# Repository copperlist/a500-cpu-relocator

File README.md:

# CopperList CPU-01: Amiga 500 68000 CPU relocator

CPU-01 is CopperList's build of [LinuxJedi's Open68000Relocator](https://github.com/LinuxJedi/Open68000Relocator)
(v2c), which is itself based on [SukkoPera's Open68000Relocator](https://github.com/SukkoPera/Open68000Relocator).
It plugs into the Amiga 500's 68000 socket and turns the CPU 90 degrees, so accelerators such as the TF534 and
TF536 fit. The circuit, the 4-layer routing and LinuxJedi's markings are unchanged; the changes are listed below.

Like the original, CPU-01 is open hardware under the GNU GPL v3 (see [LICENSE](LICENSE)).

## Changes from LinuxJedi's v2c

1. **0805 capacitors.** C1 and C2 (100 nF decoupling, on the underside) use KiCad's 0805 hand-solder footprint
   instead of 0603, in the same places and on the same nets.
2. **Clear CPU outlines and pin-1 notches.**
   - Original CPU position (the pins that go into the motherboard socket): a full outline with a large filled
     pin-1 notch, on the underside (what you see when lining the board up with the socket) and on the top. On
     the top it stops where the relocated socket's outline starts.
   - Relocated socket (where the CPU goes): the outline is redrawn with a large filled notch, kept clear of the
     board edge so it is not trimmed. Upstream's notch was 2 mm across in a 0.12 mm line, half on the edge.
   - Outlines are 0.2 mm wide and kept clear of pads and text.
3. **Design-rule clean-up.** KiCad's DRC now reports nothing but the intended overlap of the two 64-pin
   footprints (also listed as an exclusion in the project):
   - A11's meander on In1.Cu had a 0.05 mm hump 0.13 mm from A8 (the board's rule is 0.15 mm). It is now
     straight, which makes A11 about 0.16 mm shorter (about 1 ps, negligible).
   - Four dead-end track stubs (D1, DTACK, BG, BERR, 0.2 to 1.1 mm long) are removed. No connection changes.
   - No silkscreen over pads.
4. **CopperList markings on the underside:** bare-copper CopperList wordmark (letters exposed, their counters
   copper under the mask so they match the pour), copperlist.com, part number and
   version (CPU-01 v0.1), and the licence. LinuxJedi's own text and logos on the top are kept.

The board file is now in KiCad 7 format (upstream was KiCad 6 / 5.99).

## Ordering (JLCPCB)

Files are in [`cpu01/jlc/`](cpu01/jlc): `CPU-01_v0.1_gerbers.zip`, plus `CPU-01_v0.1_BOM.csv` and
`CPU-01_v0.1_CPL.csv` if you want JLC to fit the two capacitors.

- 4 layers, **1.6 mm** thick. (The board file's stack-up says 4.69 mm; that is a leftover default, ignore it.)
- About 97.4 x 94.7 mm. Default capabilities are enough: 0.25 mm tracks, 0.15 mm clearance, 0.4 mm via drills.
- No impedance control needed.

## Parts

| Ref | Part | Notes |
| --- | --- | --- |
| C1, C2 | 100 nF 50 V X7R, 0805 | LCSC C49678 (JLC basic part). Underside. |
| U1 | 2 x 32 round machined (turned) male pin strips, 0.9" row spacing | Underneath, into the motherboard's CPU socket. LCSC C9742 (BOOMELE 2.54-1*40P, 1x40 round pin, gold): two per board, cut to 32. |
| U2 | 2 x 32 round-hole machined female strips (or a 64-pin 0.9" DIP socket) | On top, for the 68000 or accelerator. LCSC C7495233 (CONNFLY DS1002-01-1x40V13-JK, 1x40): two per board, cut to 32. |

Holes for the pins are 0.8 mm.

## Building the files

`cpu01/build.sh` rebuilds everything from LinuxJedi's original board (`cpu01/upstream/68000Relocator.kicad_pcb`):
it applies the changes (`cpu01/tools/apply_cpu01.py`), runs DRC, exports Gerbers and drill files, writes the JLC
files and the previews. It needs KiCad 7 (kicad-cli and the pcbnew Python module, with KiCad's footprint
libraries), gerbv, and Python with shapely and Pillow.

---

# Upstream README (LinuxJedi's Open68000Relocator)
Open68000Relocator is an Open Hardware adapter PCB that changes the orientation of a 68000 DIP CPU.

**Note**: This project requires KiCad 5.99 or higher.

## Summary
This is based on [SukkoPera's](https://github.com/SukkoPera/Open68000Relocator) awesome 68000 relocator. I modified it to make it easier to fit on some motherboards and better support for PiStorm. It has the following changes:

* Hole for the capacitor C816 in rev 6 and 8 Amiga 500s (and Plus).
* Re-routed 4-layer with length adjusted traces for stability with PiStorm on some Amigas.
* Better power traces, useful for PiStorm.
* Some style changes.
* A couple of decoupling capacitors (2x 100nF 0603).

## License
Open68000Relocator is Open Hardware released under the GNU General Public License (GPL) v3. If you make any modifications to the board, **you must** contribute them back.

Open68000Relocator is provided to you ‘as is’ and without any express or implied warranties whatsoever with respect to its functionality, operability or use, including, without limitation, any implied warranties of merchantability, fitness for a particular purpose or infringement. We expressly disclaim any liability whatsoever for any direct, indirect, consequential, incidental or special damages, including, without limitation, lost revenues, lost profits, losses resulting from business interruption or loss of data, regardless of the form of action or legal theory under which the liability may be asserted, even if advised of the possibility or likelihood of such damages.

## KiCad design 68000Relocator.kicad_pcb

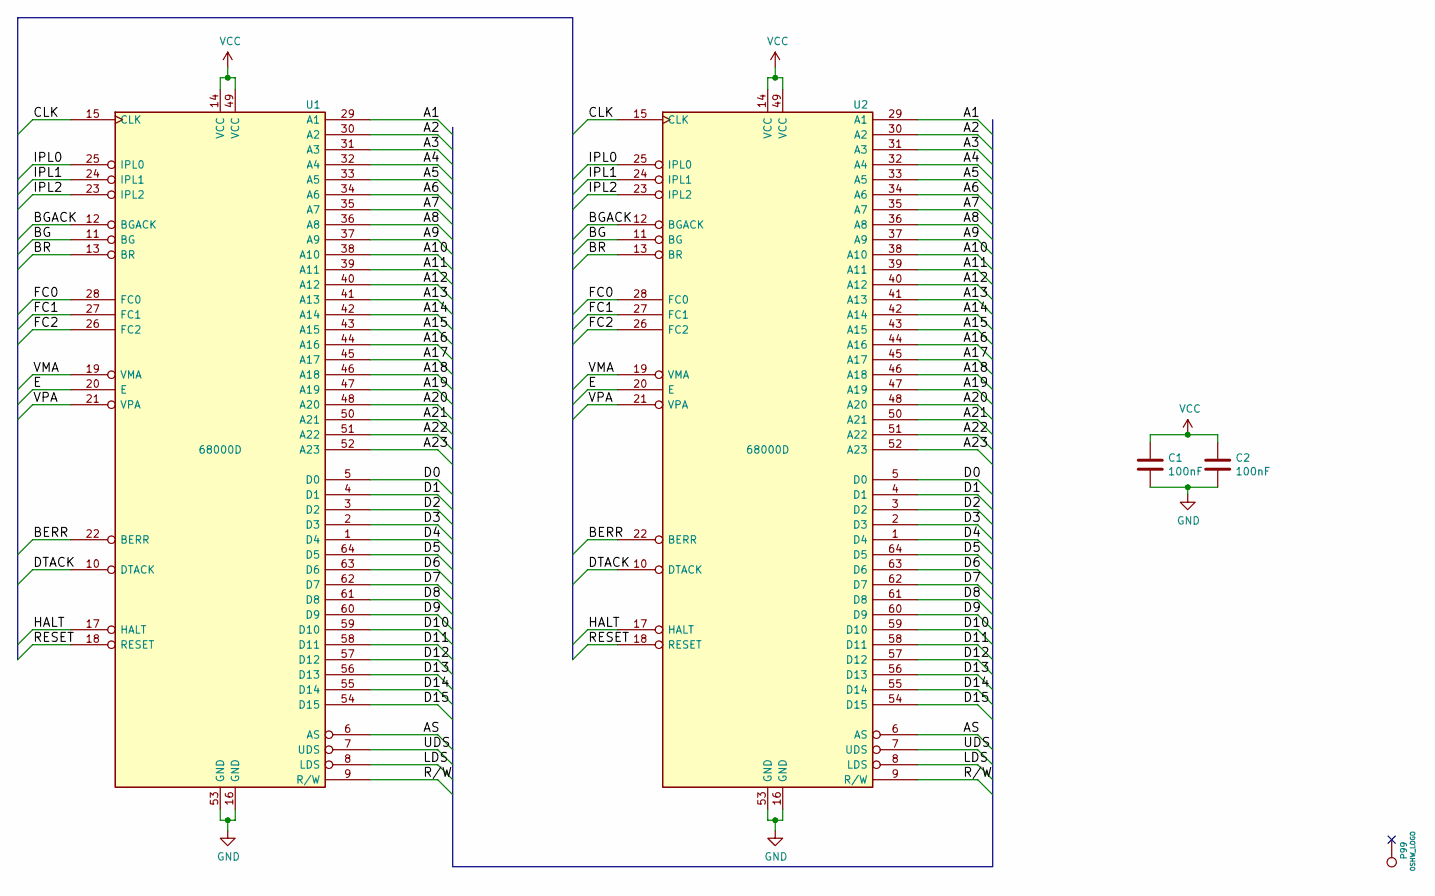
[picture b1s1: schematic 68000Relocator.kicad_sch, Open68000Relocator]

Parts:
C1, C2: 100nF; C_0805_2012Metric_Pad1.18x1.45mm_HandSolder
P99: OSHW_LOGO; OSHW-Logo_11.4x12mm_Copper
U1: 68000D; DIP-64_W22.86mm_Socket_LongPads_Socket
U2: 68000D; DIP-64_W22.86mm_Socket_LongPads_IC

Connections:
/A1: U1.29 (A1), U2.29 (A1)
/A2: U1.30 (A2), U2.30 (A2)
/A3: U1.31 (A3), U2.31 (A3)
/A4: U1.32 (A4), U2.32 (A4)
/A5: U1.33 (A5), U2.33 (A5)
/A6: U1.34 (A6), U2.34 (A6)
/A7: U1.35 (A7), U2.35 (A7)
/A8: U1.36 (A8), U2.36 (A8)
/A9: U1.37 (A9), U2.37 (A9)
/A10: U1.38 (A10), U2.38 (A10)
/A11: U1.39 (A11), U2.39 (A11)
/A12: U1.40 (A12), U2.40 (A12)
/A13: U1.41 (A13), U2.41 (A13)
/A14: U1.42 (A14), U2.42 (A14)
/A15: U1.43 (A15), U2.43 (A15)
/A16: U1.44 (A16), U2.44 (A16)
/A17: U1.45 (A17), U2.45 (A17)
/A18: U1.46 (A18), U2.46 (A18)
/A19: U1.47 (A19), U2.47 (A19)
/A20: U1.48 (A20), U2.48 (A20)
/A21: U1.50 (A21), U2.50 (A21)
/A22: U1.51 (A22), U2.51 (A22)
/A23: U1.52 (A23), U2.52 (A23)
/AS: U1.6 (AS), U2.6 (AS)
/BERR: U1.22 (BERR), U2.22 (BERR)
/BG: U1.11 (BG), U2.11 (BG)
/BGACK: U1.12 (BGACK), U2.12 (BGACK)
/BR: U1.13 (BR), U2.13 (BR)
/CLK: U1.15 (CLK), U2.15 (CLK)
/D0: U1.5 (D0), U2.5 (D0)
/D1: U1.4 (D1), U2.4 (D1)
/D2: U1.3 (D2), U2.3 (D2)
/D3: U1.2 (D3), U2.2 (D3)
/D4: U1.1 (D4), U2.1 (D4)
/D5: U1.64 (D5), U2.64 (D5)
/D6: U1.63 (D6), U2.63 (D6)
/D7: U1.62 (D7), U2.62 (D7)
/D8: U1.61 (D8), U2.61 (D8)
/D9: U1.60 (D9), U2.60 (D9)
/D10: U1.59 (D10), U2.59 (D10)
/D11: U1.58 (D11), U2.58 (D11)
/D12: U1.57 (D12), U2.57 (D12)
/D13: U1.56 (D13), U2.56 (D13)
/D14: U1.55 (D14), U2.55 (D14)
/D15: U1.54 (D15), U2.54 (D15)
/DTACK: U1.10 (DTACK), U2.10 (DTACK)
/E: U1.20 (E), U2.20 (E)
/FC0: U1.28 (FC0), U2.28 (FC0)
/FC1: U1.27 (FC1), U2.27 (FC1)
/FC2: U1.26 (FC2), U2.26 (FC2)
/HALT: U1.17 (HALT), U2.17 (HALT)
/IPL0: U1.25 (IPL0), U2.25 (IPL0)
/IPL1: U1.24 (IPL1), U2.24 (IPL1)
/IPL2: U1.23 (IPL2), U2.23 (IPL2)
/LDS: U1.8 (LDS), U2.8 (LDS)
/RESET: U1.18 (RESET), U2.18 (RESET)
/R/W: U1.9 (R/W), U2.9 (R/W)
/UDS: U1.7 (UDS), U2.7 (UDS)
/VMA: U1.19 (VMA), U2.19 (VMA)
/VPA: U1.21 (VPA), U2.21 (VPA)
GND: C1.2, C2.2, U1.16 (GND), U1.53 (GND), U2.16 (GND), U2.53 (GND)
VCC: C1.1, C2.1, U1.14 (VCC), U1.49 (VCC), U2.14 (VCC), U2.49 (VCC)

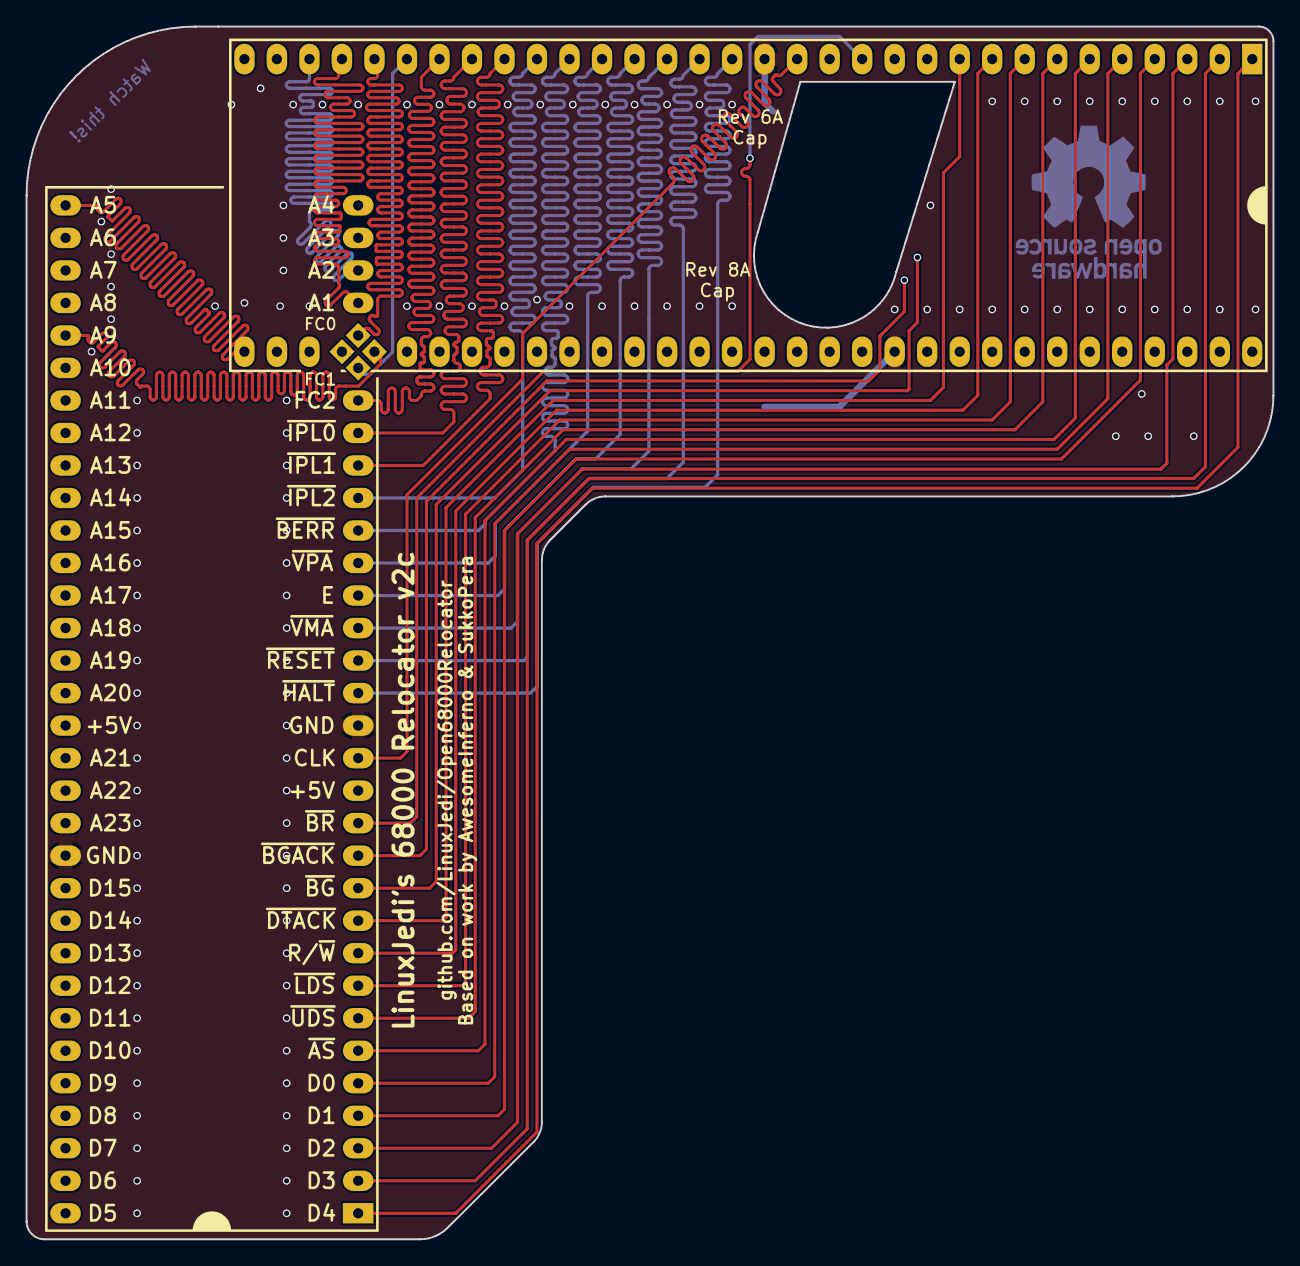
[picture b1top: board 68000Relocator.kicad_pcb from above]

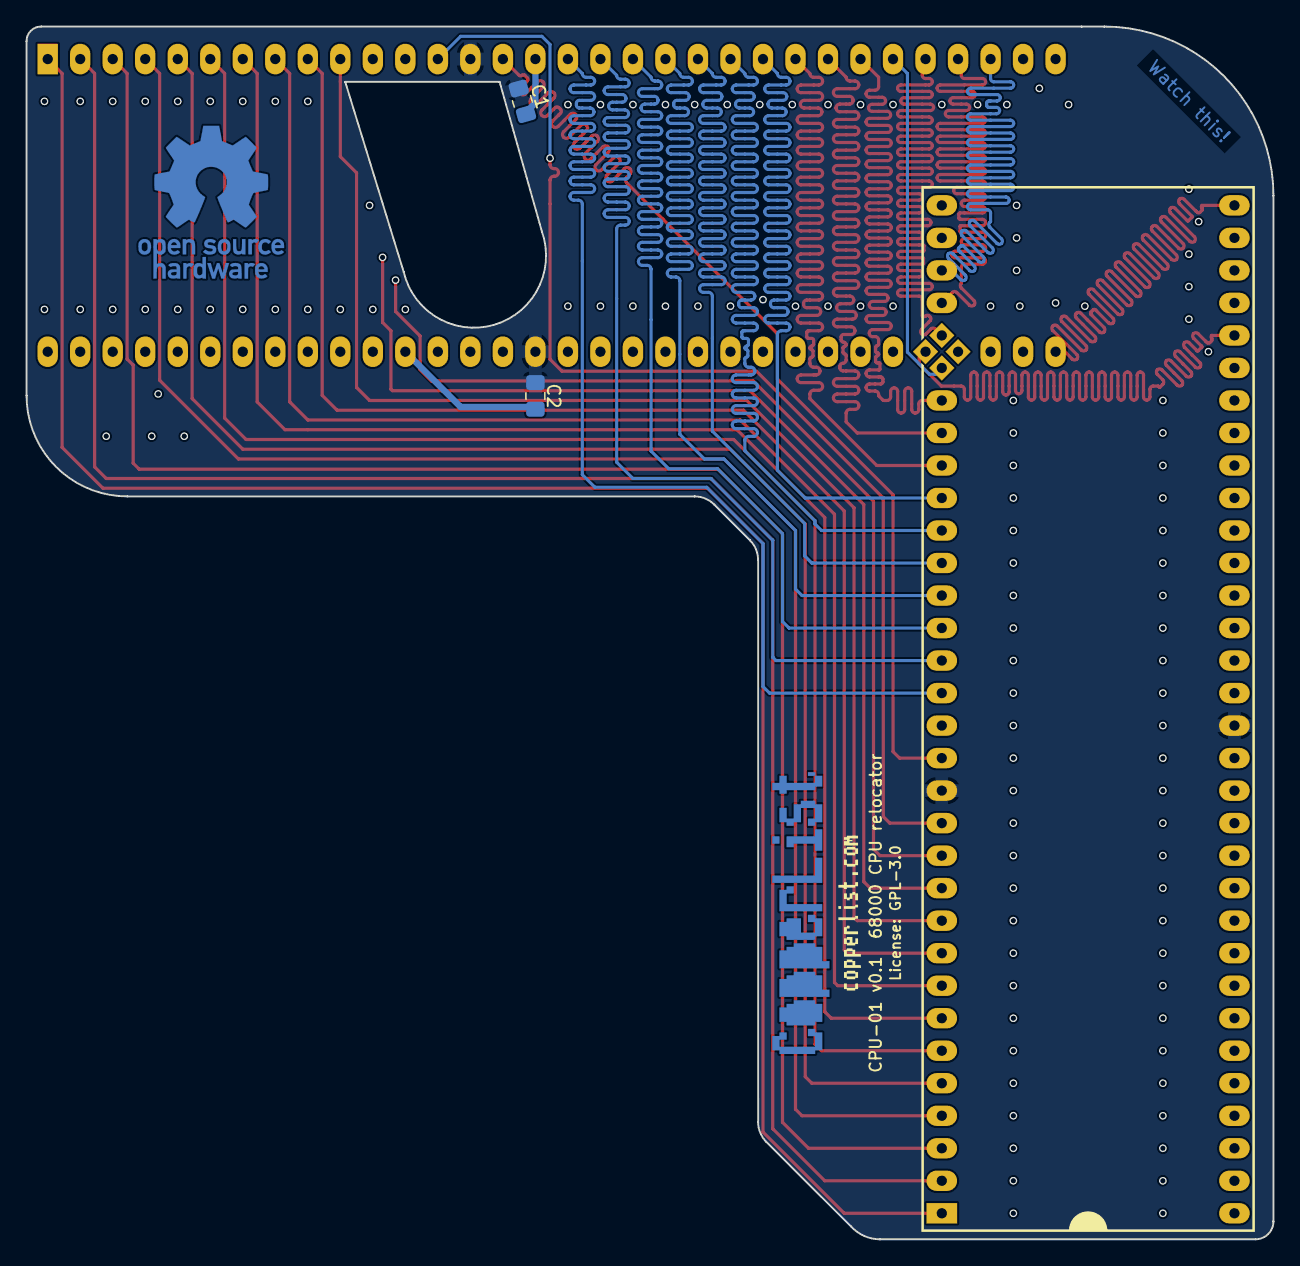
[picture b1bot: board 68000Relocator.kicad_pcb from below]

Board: 4 copper layers, 97.4 x 94.7 mm, 6 parts (3 on the bottom side), 62 nets.

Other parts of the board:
LOGO1: CopperList wordmark; CopperList_Wordmark_CPU01

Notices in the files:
68000Relocator.kicad_pcb:
License: GPL-3.0
